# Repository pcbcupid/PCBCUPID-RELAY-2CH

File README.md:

# GMOD-RELAY-2CH

This repo contains open source PCB files for PCBCUPID GMOD 2CH Relay Module <br/>
This particular PCB is designed using Kicad v9.0

**This design has been built and tested successfully!**
For more details, check out the product pages at

   * [Gmod-Relay-2CH](https://shop.pcbcupid.com/product/gm002/)

We are here to build India's largest open source hardware community, If you like to support
please consider buying the product from the above link!

[Creative Commons Attribution, Share-Alike license](https://creativecommons.org/licenses/by-sa/4.0/deed.en)
All text above must be included in any redistribution

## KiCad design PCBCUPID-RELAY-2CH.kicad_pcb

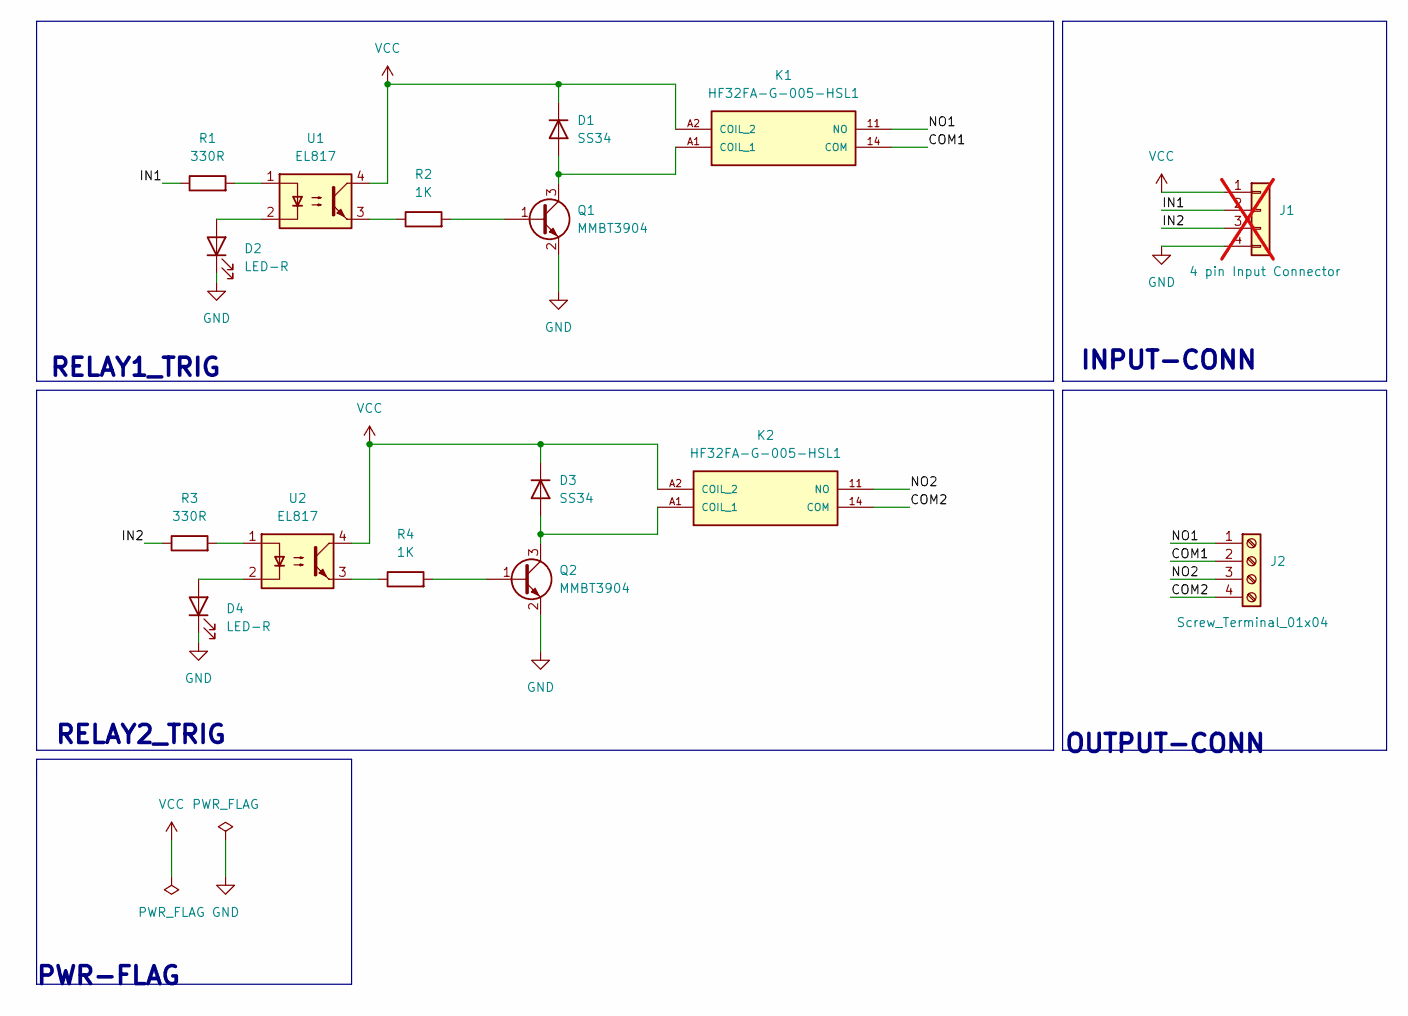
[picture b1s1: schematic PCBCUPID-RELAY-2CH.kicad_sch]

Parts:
D1, D3: SS34; D_SMA
D2, D4: LED-R; LED_0603_1608Metric
J1: 4 pin Input Connector; PinHeader_1x04_P2.54mm_Vertical; not fitted
J2: Screw_Terminal_01x04; TerminalBlock_bornier-4_P5.08mm
K1, K2: HF32FA-G-005-HSL1; HF32FA-G
Q1, Q2: MMBT3904; SOT-23
R1, R3: 330R; R_0603_1608Metric
R2, R4: 1K; R_0603_1608Metric
U1, U2: EL817; SMDIP-4_W9.53mm

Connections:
/COM1: J2.2, K1.14 (COM)
/COM2: J2.4, K2.14 (COM)
/IN1: J1.2, R1.1
/IN2: J1.3, R3.1
/NO1: J2.1, K1.11 (NO)
/NO2: J2.3, K2.11 (NO)
GND: D2.1 (K), D4.1 (K), J1.4, Q1.2 (E), Q2.2 (E)
unnamed: D1.2 (A), K1.A1 (COIL_1), Q1.3 (C)
unnamed: D2.2 (A), U1.2
unnamed: D3.2 (A), K2.A1 (COIL_1), Q2.3 (C)
unnamed: D4.2 (A), U2.2
unnamed: Q1.1 (B), R2.2
unnamed: Q2.1 (B), R4.2
unnamed: R1.2, U1.1
unnamed: R2.1, U1.3
unnamed: R3.2, U2.1
unnamed: R4.1, U2.3
VCC: D1.1 (K), D3.1 (K), J1.1, K1.A2 (COIL_2), K2.A2 (COIL_2), U1.4, U2.4

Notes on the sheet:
RELAY2_TRIG
PWR-FLAG
INPUT-CONN
OUTPUT-CONN
RELAY1_TRIG

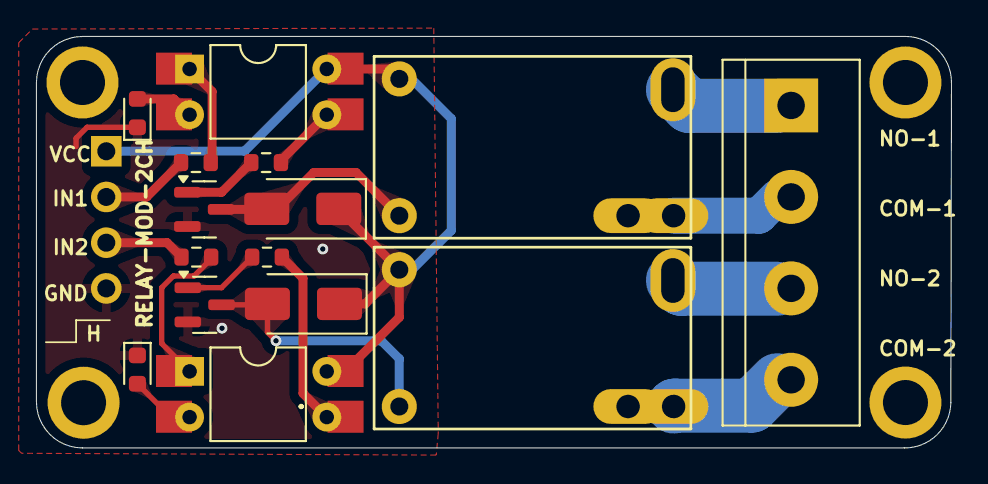
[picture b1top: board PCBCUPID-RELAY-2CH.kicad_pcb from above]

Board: 2 copper layers, 50.8 x 22.9 mm, 16 parts (0 on the bottom side), 18 nets.

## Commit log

2025-06-28 Initial Upload
